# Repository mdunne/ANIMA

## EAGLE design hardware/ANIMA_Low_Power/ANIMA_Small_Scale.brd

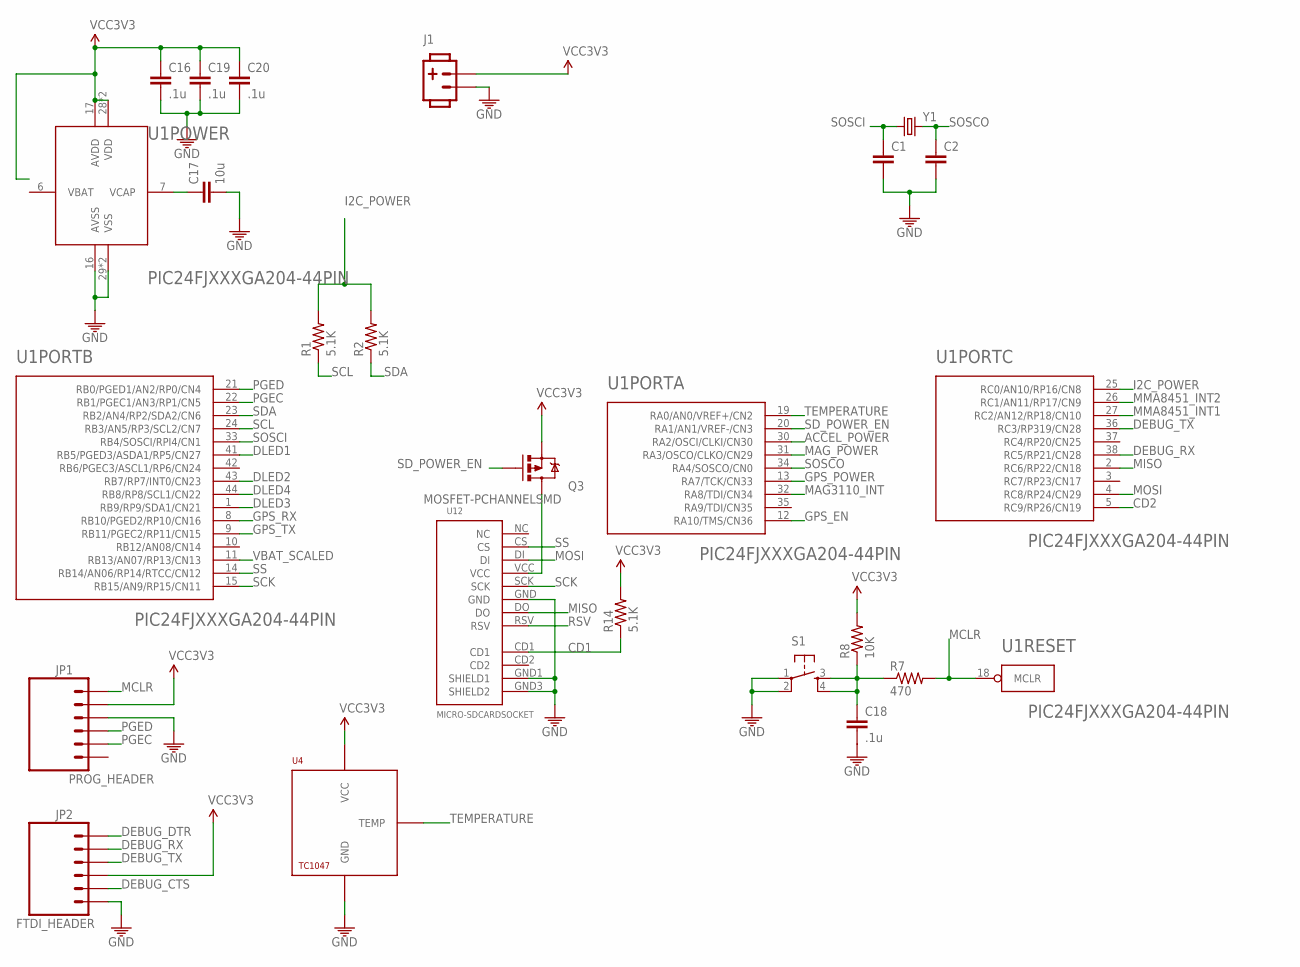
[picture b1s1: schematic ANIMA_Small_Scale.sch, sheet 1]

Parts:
C1, C2: CAP0805; 0805
C16, C18, C19, C20: .1u; 0805
C17: 10u; 0805
J1: POW_CONNECTFEMALE-RA; SOCKET-FEMALE_RA-3.96MM-2
JP1, JP2: M06FEMALE_LOCK; 1X06_FEMALE_LOCK.010
Q3: MOSFET-PCHANNELSMD; SOT23-3
R1, R2, R14: 5.1K; 0805
R7: 470; 0805
R8: 10K; 0805
S1: TAC_SWITCHPTH; B3F-1020
U1: PIC24FJXXXGA204-44PIN; TQFP44
U4: TC1047; SOT-23B
U12: MICRO-SDCARDSOCKET; MICRO-SD-SOCKET-PP
Y1: CRYSTALABS07; CRYSTAL-ABS07

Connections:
ACCEL_POWER: U1.30 (RA2/OSCI/CLKI/CN30); also elsewhere on the board
CD1: R14.1, U12.CD1
CD2: U1.5 (RC9/RP26/CN19)
DEBUG_CTS: JP2.5
DEBUG_DTR: JP2.1
DEBUG_RX: JP2.2, U1.38 (RC5/RP21/CN28)
DEBUG_TX: JP2.3, U1.36 (RC3/RP319/CN28)
DLED1: U1.41 (RB5/PGED3/ASDA1/RP5/CN27); also elsewhere on the board
DLED2: U1.43 (RB7/RP7/INT0/CN23); also elsewhere on the board
DLED3: U1.1 (RB9/RP9/SDA1/CN21); also elsewhere on the board
DLED4: U1.44 (RB8/RP8/SCL1/CN22); also elsewhere on the board
GND: C1.2, C2.2, C16.2, C17.2, C18.2, C19.2, C20.2, J1.2, JP1.3, JP2.6, S1.1, S1.2, U1.16 (AVSS), U1.29 (VSS), U1.39 (VSS), U4.P$3 (GND), U12.GND, U12.GND1 (SHIELD1), U12.GND3 (SHIELD2); also elsewhere on the board
GPS_EN: U1.12 (RA10/TMS/CN36); also elsewhere on the board
GPS_POWER: U1.13 (RA7/TCK/CN33); also elsewhere on the board
GPS_RX: U1.8 (RB10/PGED2/RP10/CN16); also elsewhere on the board
GPS_TX: U1.9 (RB11/PGEC2/RP11/CN15); also elsewhere on the board
I2C_POWER: R1.2, R2.2, U1.25 (RC0/AN10/RP16/CN8)
MAG3110_INT: U1.32 (RA8/TDI/CN34); also elsewhere on the board
MAG_POWER: U1.31 (RA3/OSCO/CLKO/CN29); also elsewhere on the board
MCLR: JP1.1, R7.2, U1.18 (MCLR)
MISO: U1.2 (RC6/RP22/CN18), U12.DO
MMA8451_INT1: U1.27 (RC2/AN12/RP18/CN10); also elsewhere on the board
MMA8451_INT2: U1.26 (RC1/AN11/RP17/CN9); also elsewhere on the board
MOSI: U1.4 (RC8/RP24/CN29), U12.DI
unnamed: C18.1, R7.1, R8.1, S1.3, S1.4
unnamed: C17.1, U1.7 (VCAP)
unnamed: Q3.3 (D), U12.VCC
PGEC: JP1.5, U1.22 (RB1/PGEC1/AN3/RP1/CN5)
PGED: JP1.4, U1.21 (RB0/PGED1/AN2/RP0/CN4)
RSV: U12.RSV
SCK: U1.15 (RB15/AN9/RP15/CN11), U12.SCK
SCL: R1.1, U1.24 (RB3/AN5/RP3/SCL2/CN7); also elsewhere on the board
SDA: R2.1, U1.23 (RB2/AN4/RP2/SDA2/CN6); also elsewhere on the board
SD_POWER_EN: Q3.1 (G), U1.20 (RA1/AN1/VREF-/CN3)
SOSCI: C1.1, U1.33 (RB4/SOSCI/RPI4/CN1), Y1.P$1 (1)
SOSCO: C2.1, U1.34 (RA4/SOSCO/CN0), Y1.P$2 (2)
SS: U1.14 (RB14/AN06/RP14/RTCC/CN12), U12.CS
TEMPERATURE: U1.19 (RA0/AN0/VREF+/CN2), U4.P$2 (TEMP)
VBAT_SCALED: U1.11 (RB13/AN07/RP13/CN13)
VCC3V3: C16.1, C19.1, C20.1, J1.1, JP1.2, JP2.4, Q3.2 (S), R8.2, R14.2, U1.17 (AVDD), U1.28 (VDD), U1.40 (VDD), U4.P$1 (VCC); also elsewhere on the board

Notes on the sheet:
PROG_HEADER
FTDI_HEADER

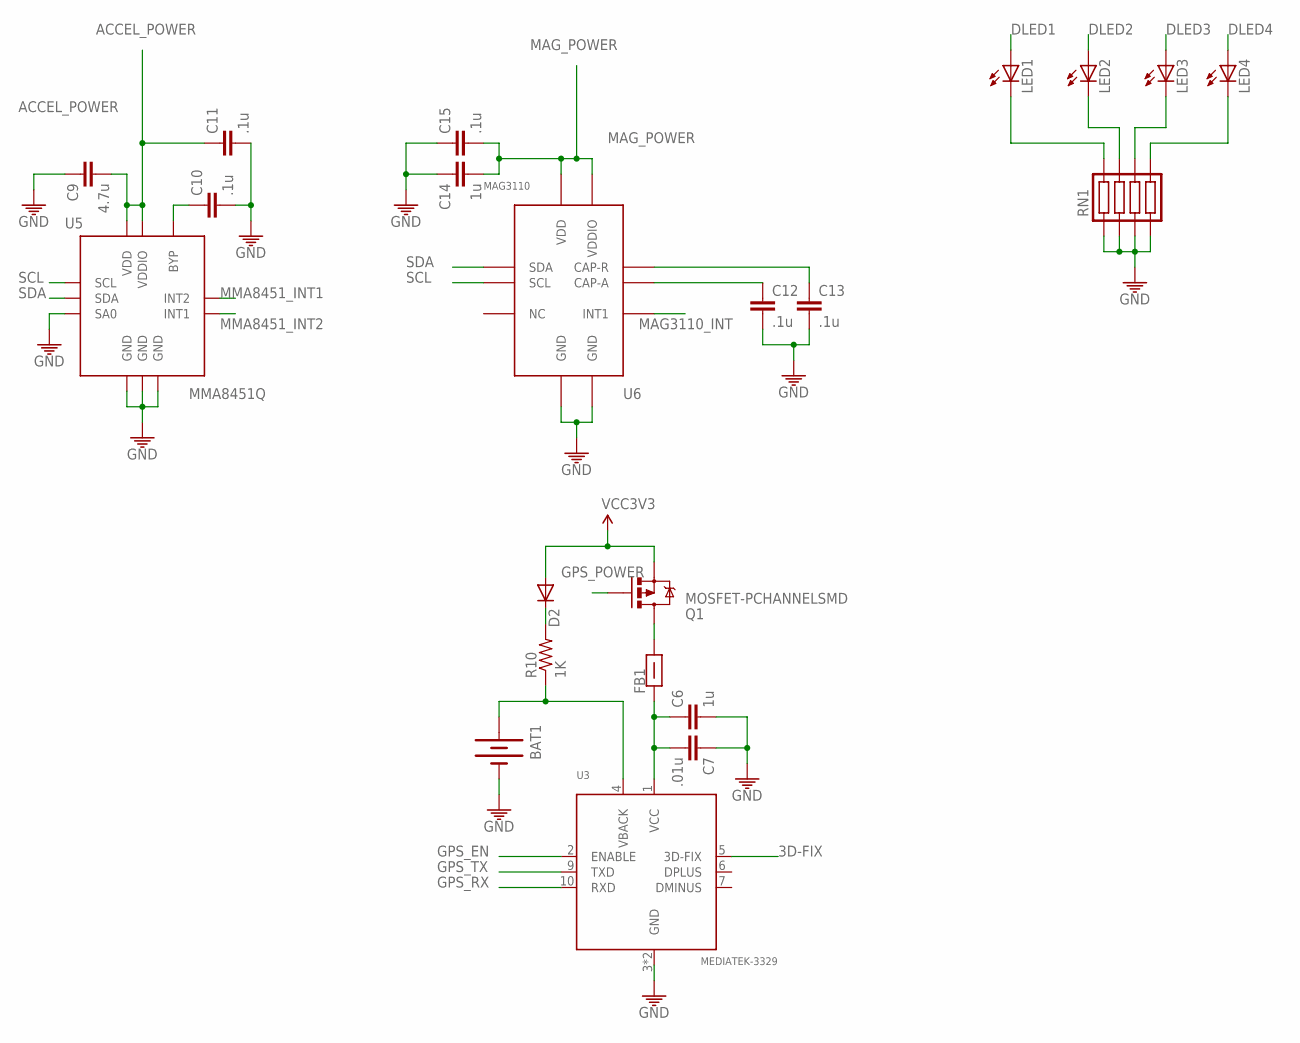
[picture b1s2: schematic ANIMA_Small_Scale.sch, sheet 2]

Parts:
BAT1: BATTERY4.8MMSMD; MS412FE-FL26E
C6, C14: 1u; 0805
C7: .01u; 0805
C9: 4.7u; 0805
C10, C11, C12, C13, C15: .1u; 0805
D2: DIODESMA; SMA-DIODE
FB1: FERRITE_BEAD; 0603
LED1, LED2, LED3, LED4: LED1206; LED-1206
Q1: MOSFET-PCHANNELSMD; SOT23-3
R10: 1K; 0805
RN1: RESISTOR_ARRAY-4; EXB-38V271JV
U3: MEDIATEK-3329
U5: MMA8451Q; QFN-16_FREE
U6: MAG3110; DFN-10_FREE

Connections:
3D-FIX: U3.5 (3D-FIX)
ACCEL_POWER: C9.2, C11.1, U5.P$1 (VDDIO), U5.P$14 (VDD); also elsewhere on the board
DLED1: LED1.A; also elsewhere on the board
DLED2: LED2.A; also elsewhere on the board
DLED3: LED3.A; also elsewhere on the board
DLED4: LED4.A; also elsewhere on the board
GND: BAT1.-, C6.2, C7.1, C9.1, C10.2, C11.2, C12.2, C13.2, C14.1, C15.1, RN1.P$1 (1), RN1.P$2 (2), RN1.P$3 (3), RN1.P$4 (4), U3.3 (GND), U3.8 (GND), U5.P$5 (GND), U5.P$7 (SA0), U5.P$10 (GND), U5.P$12 (GND), U6.P$5 (GND), U6.P$10 (GND); also elsewhere on the board
GPS_EN: U3.2 (ENABLE); also elsewhere on the board
GPS_POWER: Q1.1 (G); also elsewhere on the board
GPS_RX: U3.10 (RXD); also elsewhere on the board
GPS_TX: U3.9 (TXD); also elsewhere on the board
MAG3110_INT: U6.P$9 (INT1); also elsewhere on the board
MAG_POWER: C14.2, C15.2, U6.P$2 (VDD), U6.P$8 (VDDIO); also elsewhere on the board
MMA8451_INT1: U5.P$9 (INT2); also elsewhere on the board
MMA8451_INT2: U5.P$11 (INT1); also elsewhere on the board
unnamed: C10.1, U5.P$2 (BYP)
unnamed: C13.1, U6.P$4 (CAP-R)
unnamed: C6.1, C7.2, FB1.1, U3.1 (VCC)
unnamed: C12.1, U6.P$1 (CAP-A)
unnamed: LED4.C, RN1.P$5 (5)
unnamed: LED3.C, RN1.P$6 (6)
unnamed: LED1.C, RN1.P$8 (8)
unnamed: BAT1.+, R10.1, U3.4 (VBACK)
unnamed: LED2.C, RN1.P$7 (7)
unnamed: FB1.2, Q1.3 (D)
unnamed: D2.C, R10.2
SCL: U5.P$4 (SCL), U6.P$7 (SCL); also elsewhere on the board
SDA: U5.P$6 (SDA), U6.P$6 (SDA); also elsewhere on the board
VCC3V3: D2.A, Q1.2 (S); also elsewhere on the board

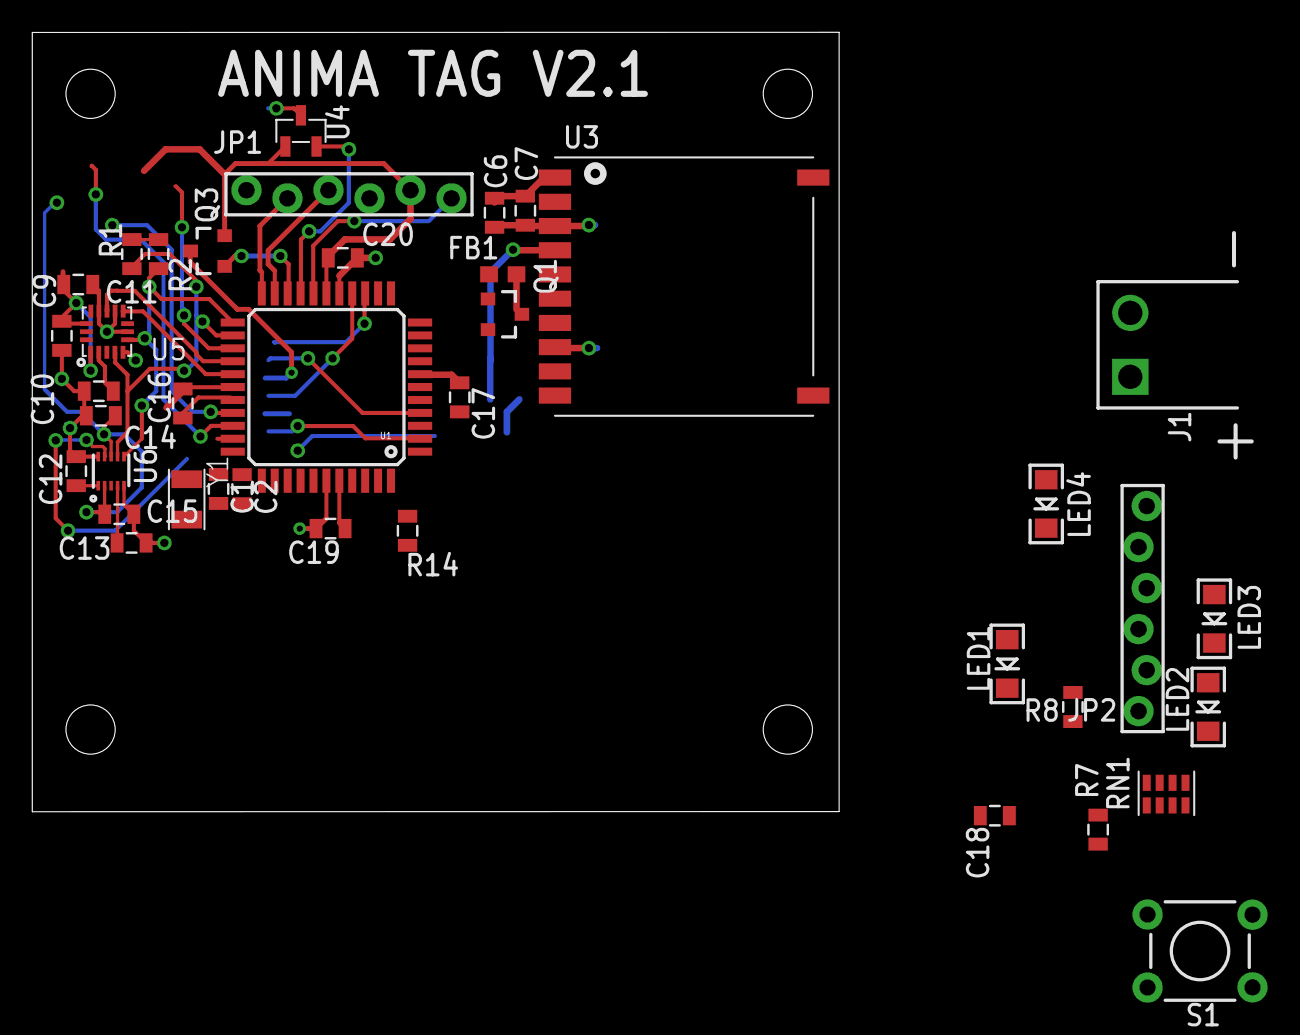
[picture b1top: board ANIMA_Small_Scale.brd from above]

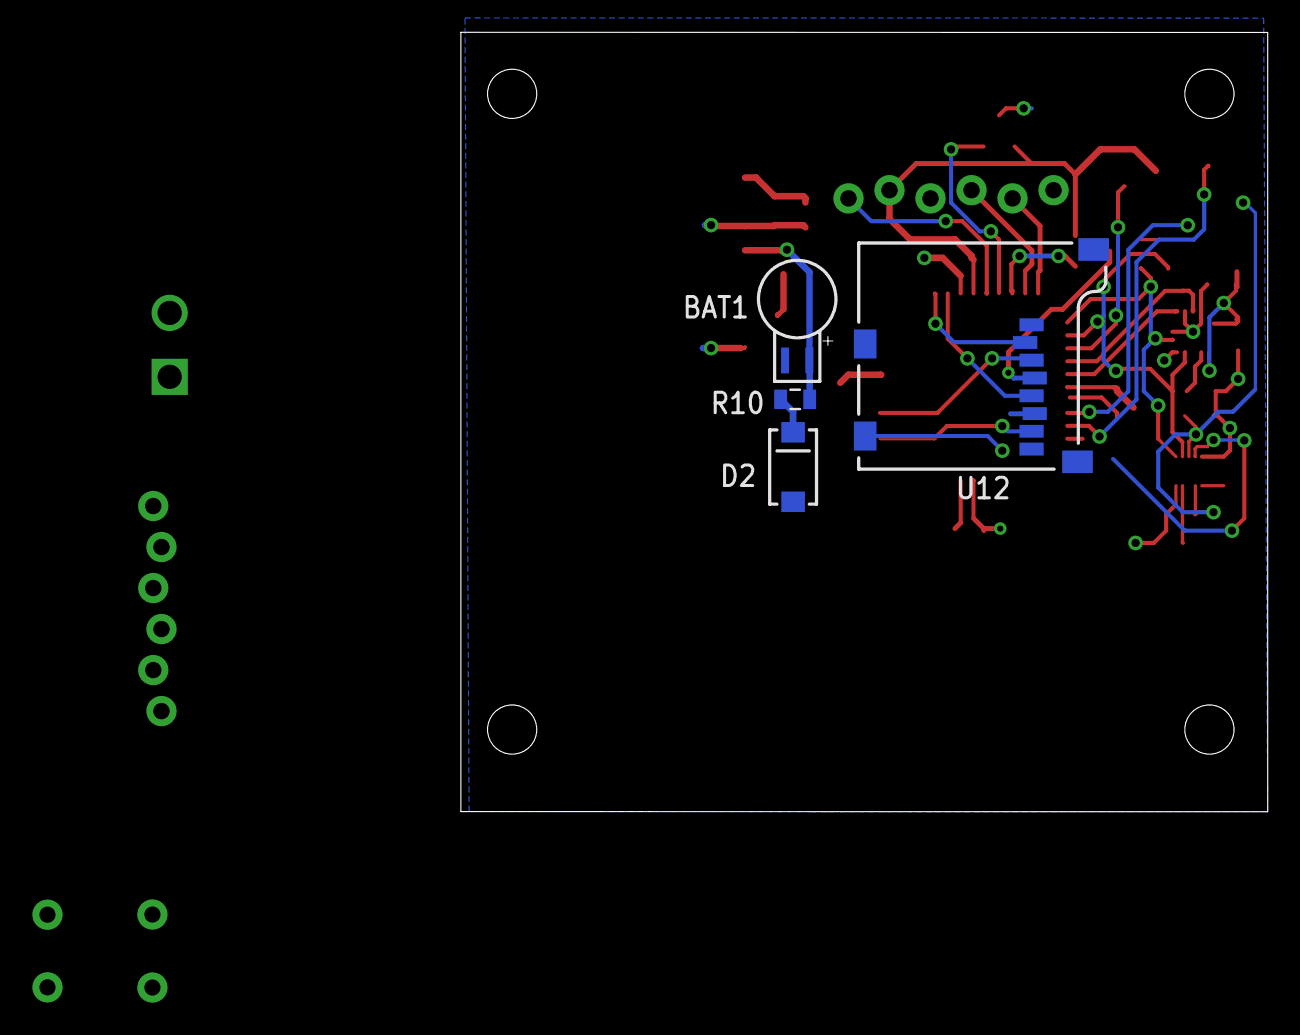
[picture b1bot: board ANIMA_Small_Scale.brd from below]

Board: 2 copper layers, 50.0 x 48.3 mm, 47 parts (4 on the bottom side), 46 nets.

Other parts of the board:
ST1, ST2, ST3, ST4: STAND-OFF-TIGHT

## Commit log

2010-09-23 initial project set-up for testing functionality of LCD Library
2010-09-24 initialized the gps module started work on the nmea parser
2010-09-28 minor updates to gps uart state machine added code from autoboat for nmea parsing needs work as currently no good way to extract the data
2010-10-01 gps parser now works and a appropriate wrapper to allow easy change of UART Port
2010-10-04 gps code updated, now works as required
2011-04-11 commit before starting development of sensor testing rig
2011-04-25 adding source files for accelerometer and magnetometer testing
2011-04-26 finished code for initial freescale accelerometer setup added additional datasheets
2011-04-26 adding MPLAB project files. Somehow were missed in original checkin
2011-05-20 addition of various datasheets
    additonal project using MPLAB X as alternative IDE
2011-05-24 added additional datasheets, changed from bma150 to bma180 due to 14 instead of 12 bit resolution
2011-08-12 still recalcitrant accelerometer
2012-01-17 added hello worlds for adxl345 and mag3110 added new datasheets
2012-01-17 added additional sensor files added blank for the sensor breakout and older library to serve as base
2012-01-19 added various new datasheets for additional sensors and re-arranged several folders made footprints for two accelerometers in eagle and adjusted the schematic
2012-04-06 added sensor breakout board and rest of library
2012-06-28 issue with deleted files
2012-06-28 added additional projects with basic functionality for a few sensors
2012-07-08 added gps along with various datasheets few more sensors libraries are up
2012-07-13 modifications to various libraries to suppress debug messages added sensor_Integration A wrapper for all the sensor taking
2012-07-15 myraid chagnes to sensor drivers added additional datasheets
2012-07-15 closed of all projects to get clean state for transfer
2012-07-16 test commit for laptop integration
2012-08-09 sensor integration complete with all sensors reading data on Uno Dev Board
2012-11-08 changeover mostly complete shifting to SD card redesign
2012-11-13 completed changeover for Data Logging with XC and new boot loader
2012-11-13 Moved SD Files into project directory instead of Microchip Directory
2013-04-11 Commit after re-install of OS and associated tools
2013-06-21 SD card now runs FAT16 again, seems to be working fine not integrated with the rest of sensor_integration
2013-06-26 modififed timers for faster timing various fixes to ensure new form of data logging continued to work
2013-07-16 update peripheral libaries to not use legacy interrupt interfaces added the I2C driver which apparently had never been added
2013-07-16 added smaller scale form of ANIMA for further development work of selected sensors
2013-07-16 added original libraries for bringing up the small scale board change over to new interrupt form for UART transmit
2013-07-18 Debug Serial Port Now Works. Needed to remove the pin from the A/D system
2013-07-23 added Pinout Translation.xlsx for ease of identifying pins fixed processor so it runs at proper speed now along with serial selected correctly with pps
2013-07-23 added I2C driver and converted to use I2C2 instead of I2C1
2014-01-08 added BOM and commit before fixing errors
2014-01-16 board renovations complete attempting to diagnose I2C again
2014-02-06 added port of data logging to small scale note: sequence of commits is not the same order as board was brought up due to some errors
2014-02-06 added ported libaries for Anima Small Scale
2014-02-28 started changeover from blocking polled SD card writes to data portion interrupt driven and non-blocking polling code
2014-03-03 broke out substates of each section of write. Still currently blocking code.
2014-03-12 finished converting rest of SD-SPI.c to use a non-blocking state machine. Additionally set up DMA for the large section of data transfer.
2014-04-15 added test code for data logging file allocation and modified gps code to work with current version
2014-05-05 sampler project added along with base code
2014-05-05 removed one hardware timer with slave second tick instead of two timers due to time bases wandering off
2014-05-20 sample now working at base level able to take handle sensors at different rates. Due to multiple timers desyncing it now slaves the slow timer to the fast one.
2014-06-08 added data encoding along with initial test code for generating crc with DMA
2014-06-12 finished switching between entry logic and functioned the crc generation
2014-06-23 data size adjusted to use whole sector remove data type and now strictly an array for intermediary step
2014-06-23 removed local copy of array to write out
2014-07-08 finished change over to polling form
2014-07-14 finished integration of logging into encoding now uses polled form of logging initial inspection of data shows data on card with header and checksum
2014-07-29 added basic data extract with naive crc implementation added proof of concept and more tests for data encoding
2014-07-30 changed to table driven from and removed requirement for bitarray
2014-08-11 added data Encoding library which had been missed changed sampler id size to 16bit due to inability to pack smaller parser reads packets naively
2014-08-11 stripped old crc Code out, fixed an end condition issue
2014-08-19 added output file writing in form required changed the parsing of packets to a config file driven form
2014-08-22 added PacketIDs.cfg. can be recreated easily enough but a static base is nice Finished parser to parse arbitrary packets given definition Created packet struct for gps and temp along with actually su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
2014-08-26 slight changes to data encoding and logging for bug fixes added in real data for the sampler along with the compiler flags to revert to fake data for debug
2014-10-08 various fixes to dataProcessing for stability fixed glitch with timing in sampler
2015-01-20 minor changes to sampler and logging due to thesis start of generic circular buffer needed for various projects
2015-01-26 copied the small scale to start work on low power varient
2015-01-26 creation of package for new processor replaced high power with low and reconnected major connections
2015-01-27 added oscillator removed connections prior to moving GPS to new position added additional parts
2015-01-27 added low power I2C temperature sensor datasheet
